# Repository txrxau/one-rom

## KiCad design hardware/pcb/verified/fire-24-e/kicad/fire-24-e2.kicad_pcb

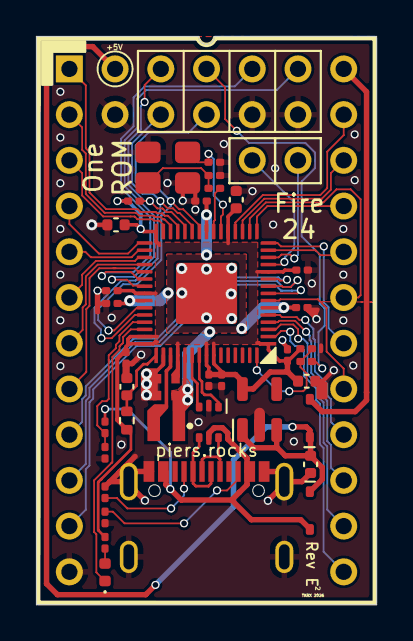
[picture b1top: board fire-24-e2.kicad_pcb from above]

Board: 2 copper layers, 18.9 x 31.6 mm, 41 parts (0 on the bottom side), 51 nets.

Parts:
C1, C2, C7, C13, C15: 4.7uF; C_0402_1005Metric
C3, C4, C5, C6, C8, C9, C10, C11, C12: 0.1uF; C_0201_0603Metric
C16, C17: 4.7uF; C_0402_1005Metric_small_pads
C18, C19: 15pF; C_0201_0603Metric
D1: LED_Small; LED_0402_1005Metric
D2, D3: 1N5819WS; D_SOD-323
J1, J3: Conn_01x02_Pin; PinHeader_1x02_P2.54mm_Vertical
J2: Conn_02x04_Odd_Even; PinHeader_2x04_P2.54mm_Vertical custom silkscreen
J4: USB_C_Receptacle_USB2.0_16P; USB_C_connector_c2765186
L1: 3.3u; L_pol_2016
R1, R3, R7, R8: 10K; R_0201_0603Metric
R2, R5, R6: 1K; R_0201_0603Metric
R4: 33R; R_0402_1005Metric
R9, R10: 5K1; R_0201_0603Metric
U1: RP2350_60QFN; RP2350-QFN-60-1EP_7x7_P0.4mm_EP3.4x3.4mm_ThermalVias
U2: 2332/2364 SOCKET; 2x12 dip pin output 600mil centres no ss
U3: AP2112K-3.3; SOT-23-5
U4: USBLC6-2P6; SOT-666
Y1: Crystal_GND24; Crystal_SMD_Abracon_ABM8G-4Pin_3.2x2.5mm

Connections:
+1V1: C3.1, C4.1, C5.1, C17.1, L1.1, U1.6 (DVDD), U1.23 (DVDD), U1.39 (DVDD), U1.50 (VREG_FB)
+3V3: C2.1, C6.1, C7.1, C8.1, C9.1, C10.1, C11.1, C12.1, C13.1, C16.1, R1.1, R3.1, R4.2, R5.1, U1.1 (IOVDD), U1.11 (IOVDD), U1.20 (IOVDD), U1.30 (IOVDD), U1.38 (IOVDD), U1.44 (ADC_AVDD), U1.45 (IOVDD), U1.49 (VREG_VIN), U1.53 (USB_OTP_VDD), U1.54 (QSPI_IOVDD), U3.5 (VOUT)
+5V: C1.1, D2.1 (K), D3.1 (K), J1.1, U3.1 (VIN), U3.3 (EN)
A0: U1.35 (GPIO23), U2.8 (A0)
A1: U1.34 (GPIO22), U2.7 (A1)
A2: U1.33 (GPIO21), U2.6 (A2)
A3: U1.32 (GPIO20), U2.5 (A3)
A4: U1.31 (GPIO19), U2.4 (A4)
A5: U1.29 (GPIO18), U2.3 (A5)
A6: U1.28 (GPIO17), U2.2 (A6)
A7: U1.27 (GPIO16), U2.1 (A7)
A8: U1.19 (GPIO15), U2.23 (A8)
A9: U1.18 (GPIO14), U2.22 (A9)
A10: U1.17 (GPIO13), U2.19 (A10)
A11_CE: U1.15 (GPIO11), U2.18 (A11)
A12_CS: U1.16 (GPIO12), U2.21 (A12)
BOOT: J2.5, R2.1
CS1_OE: U1.14 (GPIO10), U2.20 (~CS)
CX1: J3.1, U1.13 (GPIO9)
CX2: J3.2, U1.12 (GPIO8)
D0: U1.10 (GPIO7), U2.9 (D0)
D1: U1.9 (GPIO6), U2.10 (D1)
D2: U1.8 (GPIO5), U2.11 (D2)
D3: U1.2 (GPIO0), U2.13 (D3)
D4: U1.3 (GPIO1), U2.14 (D4)
D5: U1.4 (GPIO2), U2.15 (D5)
D6: U1.5 (GPIO3), U2.16 (D6)
D7: U1.7 (GPIO4), U2.17 (D7)
D+: U1.52 (USB_DP), U4.1 (I/O1)
D-: U1.51 (USB_DM), U4.3 (I/O2)
GND: C1.2, C2.2, C3.2, C4.2, C5.2, C6.2, C7.2, C8.2, C9.2, C10.2, C11.2, C12.2, C13.2, C15.2, C16.2, C17.2, C18.2, C19.2, J1.2, J2.2, J2.4, J4.A1 (GND), J4.A12 (GND), J4.B1 (GND), J4.B12 (GND), J4.S1 (SHIELD), R8.2, R9.1, R10.1, U1.47 (VREG_PGND), U1.61 (GND), U2.12 (GND), U3.2 (GND), U4.2 (GND), Y1.2, Y1.4
LED0: D1.1 (K), U1.43 (GPIO29_ADC3)
unnamed: C19.1, R6.1, Y1.1
unnamed: D1.2 (A), R5.2
unnamed: J4.A5 (CC1), R10.2
unnamed: J4.B5 (CC2), R9.2
unnamed: J4.A6 (D+), J4.B6 (D+), U4.6 (I/O1)
unnamed: J4.A7 (D-), J4.B7 (D-), U4.4 (I/O2)
unnamed: C15.1, R4.1, U1.46 (VREG_AVDD)
unnamed: L1.2, U1.48 (VREG_LX)
unnamed: C18.1, U1.21 (XIN), Y1.3
unnamed: R6.2, U1.22 (XOUT)
QSPI_SS: R2.2, R3.2, U1.60 (QSPI_SS)
RUN: J2.7, R1.2, U1.26 (RUN)
SEL_A: J2.1, U1.37 (GPIO25)
SEL_B: J2.3, U1.36 (GPIO24)
SEL_C: J2.6, U1.24 (SWCLK), U1.40 (GPIO26_ADC0)
SEL_D: J2.8, U1.25 (SWD), U1.41 (GPIO27_ADC1)
VBUS: D3.2 (A), J4.A4 (VBUS), J4.A9 (VBUS), J4.B4 (VBUS), J4.B9 (VBUS), R7.1, U4.5 (VBUS)
VBUS_DET: R7.2, R8.1, U1.42 (GPIO28_ADC2)
VHOST: D2.2 (A), U2.24 (VCC)

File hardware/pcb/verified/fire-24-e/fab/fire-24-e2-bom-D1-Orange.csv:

Reference,Qty,Value,DNP,Exclude from BOM,Exclude from Board,Footprint,Datasheet,LCSC
"C1,C2,C7,C13,C15,C16,C17",7,4.7uF,,,,Capacitor_SMD:C_0402_1005Metric,~,C23733
"C3,C4,C5,C6,C8,C9,C10,C11,C12",9,0.1uF,,,,Capacitor_SMD:C_0201_0603Metric,~,C52033358 
"C18,C19",2,15pF,,,,Capacitor_SMD:C_0201_0603Metric,~,C54110121 
D1,1,LED_Small,,,,LED_SMD:LED_0402_1005Metric,~,C965791
"D2,D3",2,1N5819WS,,,,Diode_SMD:D_SOD-323,,C191023
J4,1,USB_C_Receptacle_USB2.0_16P,,,,piers retro:USB_C_connector_c2765186,https://www.usb.org/sites/default/files/documents/usb_type-c.zip,C2765186
L1,1,3.3u,,,,RP2350_60QFN_minimal:L_pol_2016,~,C42411119
"R1,R3,R7,R8",4,10K,,,,Resistor_SMD:R_0201_0603Metric,~,C509700 
"R2,R5,R6",3,1K,,,,Resistor_SMD:R_0201_0603Metric,~,C49653491
R4,1,33R,,,,Resistor_SMD:R_0402_1005Metric,~,C25105
"R9,R10",2,5K1,,,,Resistor_SMD:R_0201_0603Metric,~,C50670521 
U1,1,RP2350_60QFN,,,,RP2350_60QFN_minimal:RP2350-QFN-60-1EP_7x7_P0.4mm_EP3.4x3.4mm_ThermalVias,, C41378174
U3,1,AP2112K-3.3,,,,Package_TO_SOT_SMD:SOT-23-5,,C51118
U4,1,USBLC6-2P6,,,,Package_TO_SOT_SMD:SOT-666,https://www.st.com/resource/en/datasheet/usblc6-2.pdf,C15999
Y1,1,Crystal_GND24,,,,Crystal:Crystal_SMD_Abracon_ABM8G-4Pin_3.2x2.5mm,~,C20625731

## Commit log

2026-06-09 none

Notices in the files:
hardware/pcb/verified/fire-24-e/kicad/fire-24-e2.kicad_pcb:
(c) 2026
